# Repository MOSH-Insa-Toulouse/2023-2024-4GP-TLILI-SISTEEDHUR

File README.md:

<h1 align="center"> Projet Capteur graphite </h1>
<h2 align="center"> TLILI Maxime - SISTEEDHUR Lakshitaa </h2>
<h3 align="center"> INSA Toulouse - département Génie Physique - 2024 </h3>

## Introduction au projet

&nbsp;&nbsp;&nbsp;&nbsp;Ce projet se construit dans le cadre de l'UF "Du capteur au banc de test" de la 4ème année du parcours Génie Physique à l'Institut National des Sciences Appliquées (INSA) de Toulouse. Il permet une approche novatrice et lowtech dans la mesure de contrainte en se basant sur les propriétés du graphite. Il s’appuie sur l’étude de capteurs de contrainte en graphite (système granulaire) dont la résistance varie suivant la déformation du capteur (Pencil Drawn Strain Gauges and Chemiresistors on Paper Cheng-Wei Lin*, Zhibo Zhao*, Jaemyung Kim & Jiaxing Huang Department of Materials Science and Engineering, Northwestern University 2220 Campus Drive, Evanston, IL, 60208, USA).

&nbsp;&nbsp;&nbsp;&nbsp;Au cours de ce projet, nous avons réalisé un dispositif permettant de relever des mesures de contrainte à partir d'une feuille en papier sur laquelle était déposée du graphène. En déformant le capteur, sa résistance est modifiée.. Il est donc possible de réaliser un capteur de déformation low-tech, que nous appellerons par la suite "capteur graphite". Dans un premier temps, nous avons simulé le comportement du circuit analogique sur le logiciel LTSpice. Ce circuit a le double rôle d’amplifier (via un amplificateur transimpédance) et de filtrer le signal délivré par le capteur. Ensuite, un code Arduino permettant la mesure de résistance et le contrôle des différents éléments du circuit (écran OLED, module Bluetooth et potentiomètre digital) a été réalisé. Nous avons préalablement testé notre circuit et le code en montant les différents éléments sur une breadboard. Ensuite, nous avons designé un PCB grâce au logiciel KiCad constituant le shield qui se fixe sur une carte Arduino UNO.

## Livrables

Les livrables du projet sont :
    - [] Le PCB du Shield Arduino
    - [] Le code Arduino permettant de faire la mesure de la résistance du capteur graphite
    - [] L'application Android pour un pilotage bluetooth du système
    - [] le banc de test du capteur
    - [] Le datasheet du capteur
    
Pour notre projet, nous avons opté pour ajouter un écran OLED servant de menu, du flex sensor commercial pour avoir un comparatif avec notre capteur, ainsi que d'un encodeur rotatoire pour différentes fonctionnalités.

## Sommaire
***
- [Matériel nécéssaire](#matériel-nécéssaire)
- [1. Simulation électronique du capteur graphite sous LTSpice](#1-simulation-électronique-du-capteur-graphite-sous-ltspice)
- [2. PCB via KiCad](#2-pcb-via-kicad)
- [3. Réalisation du Shield](#3-réalisation-du-shield)
- [4. Code Arduino](#4-code-arduino)
- [5. Application Android](#5-application-android)
- [6. Banc de test](#6-banc-de-test)
- [Datasheet](#datasheet)
- [Contact](#contact)

## Matériel nécéssaire

 - 1 Carte [Arduino UNO](https://store.arduino.cc/products/arduino-uno-rev3)
 - 1 Ecran [OLED-01](https://www.gotronic.fr/art-afficheur-oled-0-96-i2c-oled01-31506.htm)  128x64
 - 1 Amplificateur Opérationnel [LTC1050](https://www.analog.com/en/products/ltc1050.html)
 - 1 Potentiomètre Digital [MCP-41050](https://www.microchip.com/en-us/product/mcp41050)
 - 1 Module Bluetooth [HC-05](https://www.gotronic.fr/art-module-bluetooth-hc05-26097.htm)
 - 1 Encodeur Rotatoire [KY-040](https://www.az-delivery.de/fr/products/drehimpulsgeber-modul)
 - 1 Capteur [FLEXSENSOR](https://store.spectrasymbol.com/products/flex-sensor)
 - 5 Résistances (X2 100kOhm, X1 47kOhm, X1 10kOhm, X1 1kOhm)
 - 4 Condensateurs (X3 100nF, X1 1uF)
 - Crayons (HB, 2B,...)
 - Modèle papier du capteur graphite

## 1. Simulation électronique du capteur graphite sous LTSpice

&nbsp;&nbsp;&nbsp;&nbsp;Sur le logiciel LTSpice, nous avons réalisé une simulation électrique du circuit par application du schéma suivant :

La résistance variable de notre capteur étant de l'ordre du GigaOhm, le courant généré est très faible (de l'ordre de quelques nA). Afin de délivrer une tension suffisante au niveau du convertisseur analogique-numérique d'une carte Arduino UNO, il est nécessaire d'amplifier le signal en amont de la mesure. On réalise donc un amplificateur opérationnel transimpédance. Nous avons choisi le circuit amplificateur LTC 1050 au vu de ses paramètres de tension d'offset faible. Celle-ci ne doit pas fausser les valeurs de tensions que reçoit l'Arduino. Il est aussi nécessaire de réaliser un traitement du bruit lié à l'environnement de la mesure. C'est le rôle des différents filtres qui atténuent les bruits du réseau électrique et des horloges des composants.

Cette simulation nous permet de savoir que l'Arduino UNO est capable de mesurer le signal du capteur.

## 2. PCB via KiCad

### a. Création du PCB
&nbsp;&nbsp;&nbsp;&nbsp;Cette partie concerne la conception du circuit transimpédance sur Kicad 8.0 avec l'ajout de divers composants : 
- La résistance R2 a été remplacé par le potentiomètre digital MPC-41050. Il permet d'ajuster le gain du montage en simulant une résistance variable entre 0 et 50kOhms 
- Un module bluetooth HC-05 a été ajouté pour rendre possible une communication avec une application mobile
- Un écran OLED permet de faire l'interface homme-machine en affichant les informations
- Un flexsensor a été ajouté en tant que capteur témoin
- Un encodeur rotatoire ajoute des fonctionalités pour interagir avec les autres composants. ça permet de naviguer dans les menus de l'écran OLED et de lancer la mesure

A partir d'un template d'une carte Arduino UNO, il a fallu :
- Concevoir le schématique du circuit en important et en créant les symbôles pour chaque composant
- Corréler chaque composant à une empreinte réelle en fonction de ses caractéristiques physiques (nombre de pins, distance entre deux pins,...)
- Placer les composants sur la partie schématique et réaliser le routage du circuit
- Poser un plan de masse pour faire le référencement au GND
Afin de s'assurer de la validité du PCB, nous avons été contraint à l'utilisation de deux vias.

Nous avons listé ci-dessous les symbôles et empreintes des composants, ainsi que le schématique et son PCB final

### b. Symbôles et empreintes

- amplificateur transimpédance

- Capteur graphite

- Amplificateur LTC1050

- Flexsensor

- Module bluetooth HC-05

- Potentiomètre digital MPC41050

- Encodeur rotatoire KY-040

- Ecran OLED

### c. Schématique et PCB final
- Schéma complet

- PCB

- Modèle 3D

## 3. Réalisation du Shield

&nbsp;&nbsp;&nbsp;&nbsp;Une fois le schéma PCB réalisé, nous avons sorti le circuit sur un calque à l'échelle 1:1. Il a joué le rôle de masque dans la gravure chimique sur une plaquette d'époxy recouverte d'une couche de cuivre d'une épaisseur d'environ 60um. La plaquette a été couverte d'une résine positive, puis elle a été insolé aux UVs. Nous avons plongé la plaquette dans un révélateur et dans du perchlorure de fer pour s'affranchir de la partie de la résine non isolée et du cuivre non protégé. Cette opération s'est déroulée au sein du bâtiment du département du Génie Electrique et Informatique de l'INSA Toulouse.

&nbsp;&nbsp;&nbsp;&nbsp;L'étape suivante a été le perçage mécanique des trous sur la plaquette, et la soudure des différents composants. Nous avons utilisés deux forets mécaniques : un de diamètre 1mm pour les broches de connexion avec la carte Arduino, et un de diamètre 0.8mm pour tout autre trou. Pour ce qui est de nos deux vias, nous avons soudé des fils sur la partie non visible du PCB.

## 4. Code Arduino

&nbsp;&nbsp;&nbsp;&nbsp;Pour faire la mesure de la résistance, nous avons créé un programme Arduino. Lorsqu'on maintient appuyé le bouton de l'encodeur rotatoire, la mesure de résistance se fait à un intervalle d'environ une seconde. La valeur nous est transmise par le biais de l'écran OLED.

&nbsp;&nbsp;&nbsp;&nbsp;Nous avons fournis trois fichiers de code :

- [Capteur2024V1.0.1](https://github.com/MOSH-Insa-Toulouse/2023-2024-4GP-TLILI-SISTEEDHUR/tree/main/Arduino/Capteur2024V1.0.1) : c'est la version qui fournit trois menus sur l'écran OLED permettant de choisir entre le mode Mesureflex, le mode MesureCG, et le mode calibration. Ce programme ne permet pas de faire de mesures. Dès lors que nous demandons de lire une mesure, l'écran OLED ne s'initialise plus et le programme plante
- [Capteur2024V2](https://github.com/MOSH-Insa-Toulouse/2023-2024-4GP-TLILI-SISTEEDHUR/tree/main/Arduino/Capteur2024V2.0/Capteur2024_V2.0) : C'est la version qui marche. Elle décrit le protocole présenté au dessus.
- [Test Components](https://github.com/MOSH-Insa-Toulouse/2023-2024-4GP-TLILI-SISTEEDHUR/tree/main/Arduino/Test%20Components/Test_OLED) : c'est un programme permettant de tester l'écran OLED.

## 5. Application Android

&nbsp;&nbsp;&nbsp;&nbsp;Nous avons réalisé une application android nommée FlexiGraphite.apk. Elle permet d'interagir par bluetooth avec le capteur graphite et de relever notamment la valeur de la résistance du capteur graphite.

Logo :

Menu de l'application :

On retrouve 3 parties sur le menu : 
- La connexion bluetooth au dessus, avec la possibilité de voir l'état de la connexion et de se déconnecter de tout appareil.
- L'onglet "Mesure" servant à y afficher les mesures de la résistance graphite.
- L'onglet "Calibration" qui permet de piloter le lancement de la calibration du gain transimpédance.

## 6. Banc de test

&nbsp;&nbsp;&nbsp;&nbsp;Afin de tester notre capteur, nous avons réalisé un banc de test. Le support est un ensemble de demi-cercles dont le rayon varie. 

Pour les crayons B et HB, on calcule la déformation en fonction du rayon du banc de test et on fait la mesure de résistance. On reporte les valeurs dans un graphe pour tracer l'évolution de la variation de résistance en fonction de la déformation.

## Datasheet
Le datasheet de notre capteur se trouve [ici](https://github.com/MOSH-Insa-Toulouse/2023-2024-4GP-TLILI-SISTEEDHUR/blob/main/Datasheet/Datasheet%20Graphite%20Flex%20Sensor.pdf). 

## **Contact:**
- Maxime Tlili : tlili@insa-toulouse.fr
- Lakshitaa Devi Sisteedhur : sisteedh@insa-toulouse.fr

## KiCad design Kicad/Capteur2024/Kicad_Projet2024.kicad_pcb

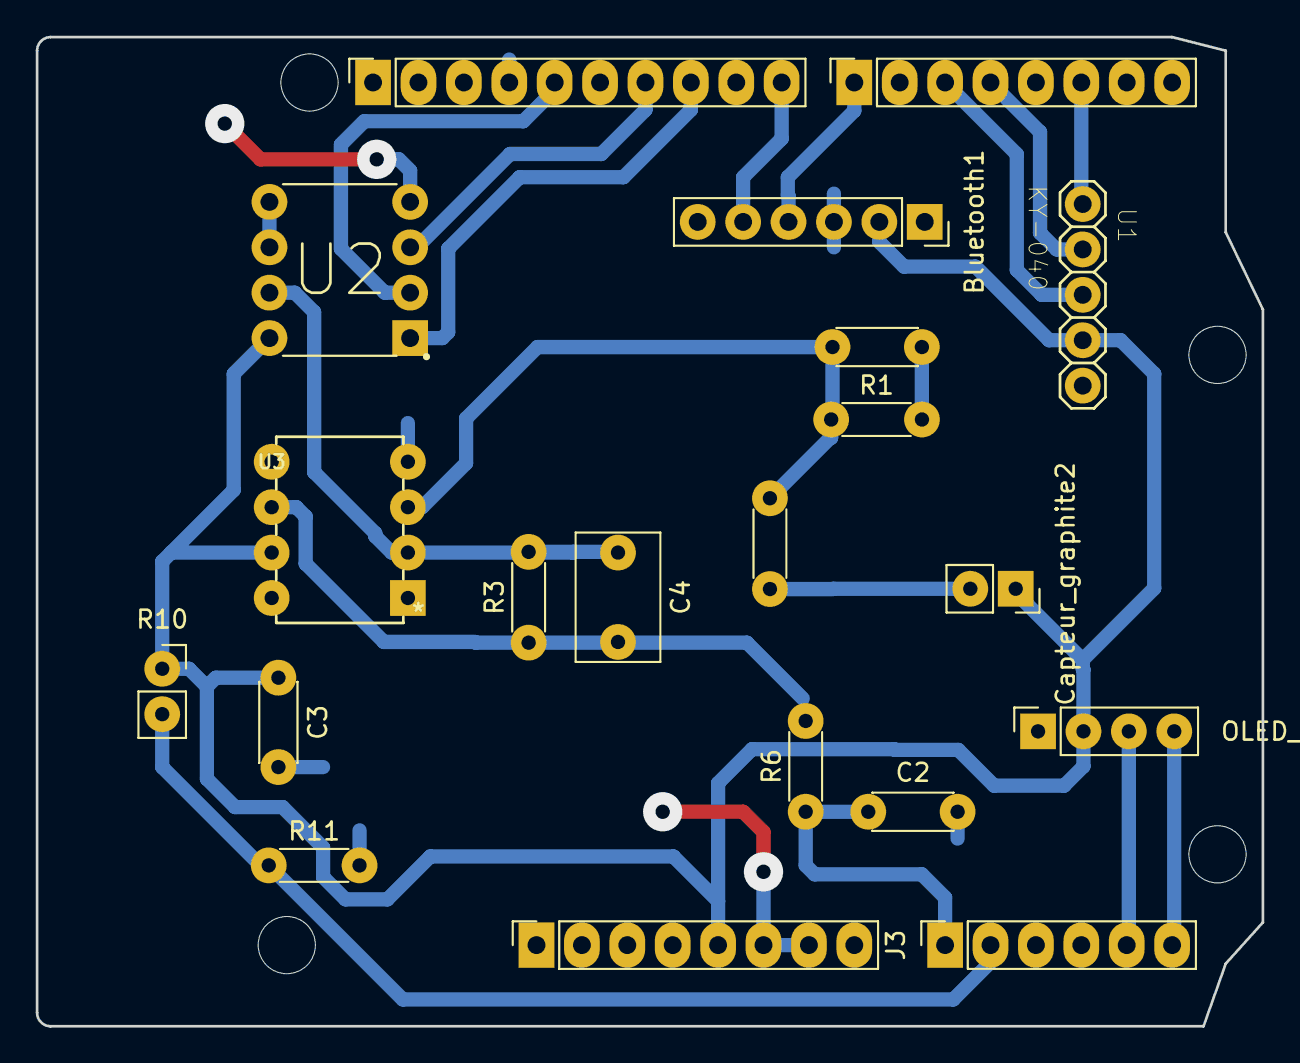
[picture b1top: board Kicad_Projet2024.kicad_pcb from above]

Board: 2 copper layers, 68.6 x 55.3 mm, 24 parts (0 on the bottom side), 18 nets.

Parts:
Bluetooth1: PinSocket_1x06_P2.54mm_Vertical
C1, C2, C3: C; C_Disc_D4.3mm_W1.9mm_P5.00mm
C4: C; C_Rect_L7.0mm_W4.5mm_P5.00mm
Capteur_graphite2: PinSocket_1x02_P2.54mm_Vertical
J1: Power; PinSocket_1x08_P2.54mm_Vertical
J2: Digital/PWM; PinSocket_1x10_P2.54mm_Vertical
J3: Analog; PinSocket_1x06_P2.54mm_Vertical
J4: Digital/PWM; PinSocket_1x08_P2.54mm_Vertical
MH1, MH2, MH3, MH4: MountingHole_3.2mm
OLED_Screen2: PinSocket_1x04_P2.54mm_Vertical
R1, R3, R5, R6, R11: R; R_Axial_DIN0204_L3.6mm_D1.6mm_P5.08mm_Horizontal
R10: FlexSensor; PinSocket_1x02_P2.54mm_Vertical
U1: KY-040; KY-040-PORT
U2: MCP41050; MPC41050_IP
U3: LTC1050CN8

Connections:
+5V: Bluetooth1.2 (Vcc), C3.1, Capteur_graphite2.1 (Vin), J1.5, OLED_Screen2.2 (VCC), R10.1, U1.VCC, U2.8 (VDD), U3.7 (V+)
/A0/ADC: C2.1, J3.1, R6.1
/A1: J3.2, R10.2, R11.1
/D2/CLK: J4.6, U1.CLK
/D4/DT: J4.4, U1.DT
/D5/SW: J4.3, U1.SW
/D10/SS: J2.8, U2.1 (~CS)
/D11/MOSI: J2.7, U2.3 (SI)
/D13/SCK: J2.5, U2.2 (SCK)
GND: Bluetooth1.3 (GND), C1.2, C2.2, C3.2, J1.6, J1.7, J2.4, OLED_Screen2.1 (GND), R1.2, R11.2, U1.GND, U2.4 (VSS), U2.5 (PA0), U2.6 (PW0), U3.4 (V-)
unnamed: Capteur_graphite2.2 (Vout), R5.1
unnamed: C1.1, R1.1, R5.2, U3.3 (+IN)
unnamed: C4.2, R3.1, R6.2, U3.6 (OUT)
R2: C4.1, R3.2, U2.7 (PB0), U3.2 (-IN)
RX: Bluetooth1.5 (RX), J2.10
SCL: J3.5, OLED_Screen2.3 (SCL)
SDA: J3.6, OLED_Screen2.4 (SDA)
TX: Bluetooth1.4 (TX), J4.1

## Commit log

2024-03-13 Add Kicad and Arduino 13/03/24
2024-04-12 Update README.md
    ajout de photos
2024-04-12 Update README.md
    ajout d'un lien
2024-04-15 Mise à Jour du GitHub
    Ajout des images, de l'état du code arduino, de la mise à jour du Kicad
2024-04-19 Update README.md
    ajout d'images pour l'application apk
2024-04-23 update GitHub 23-04-2024
2024-05-25 Update README.md
    description + détaillée
2024-05-25 Update README.md
    ajout des images du banc de test
